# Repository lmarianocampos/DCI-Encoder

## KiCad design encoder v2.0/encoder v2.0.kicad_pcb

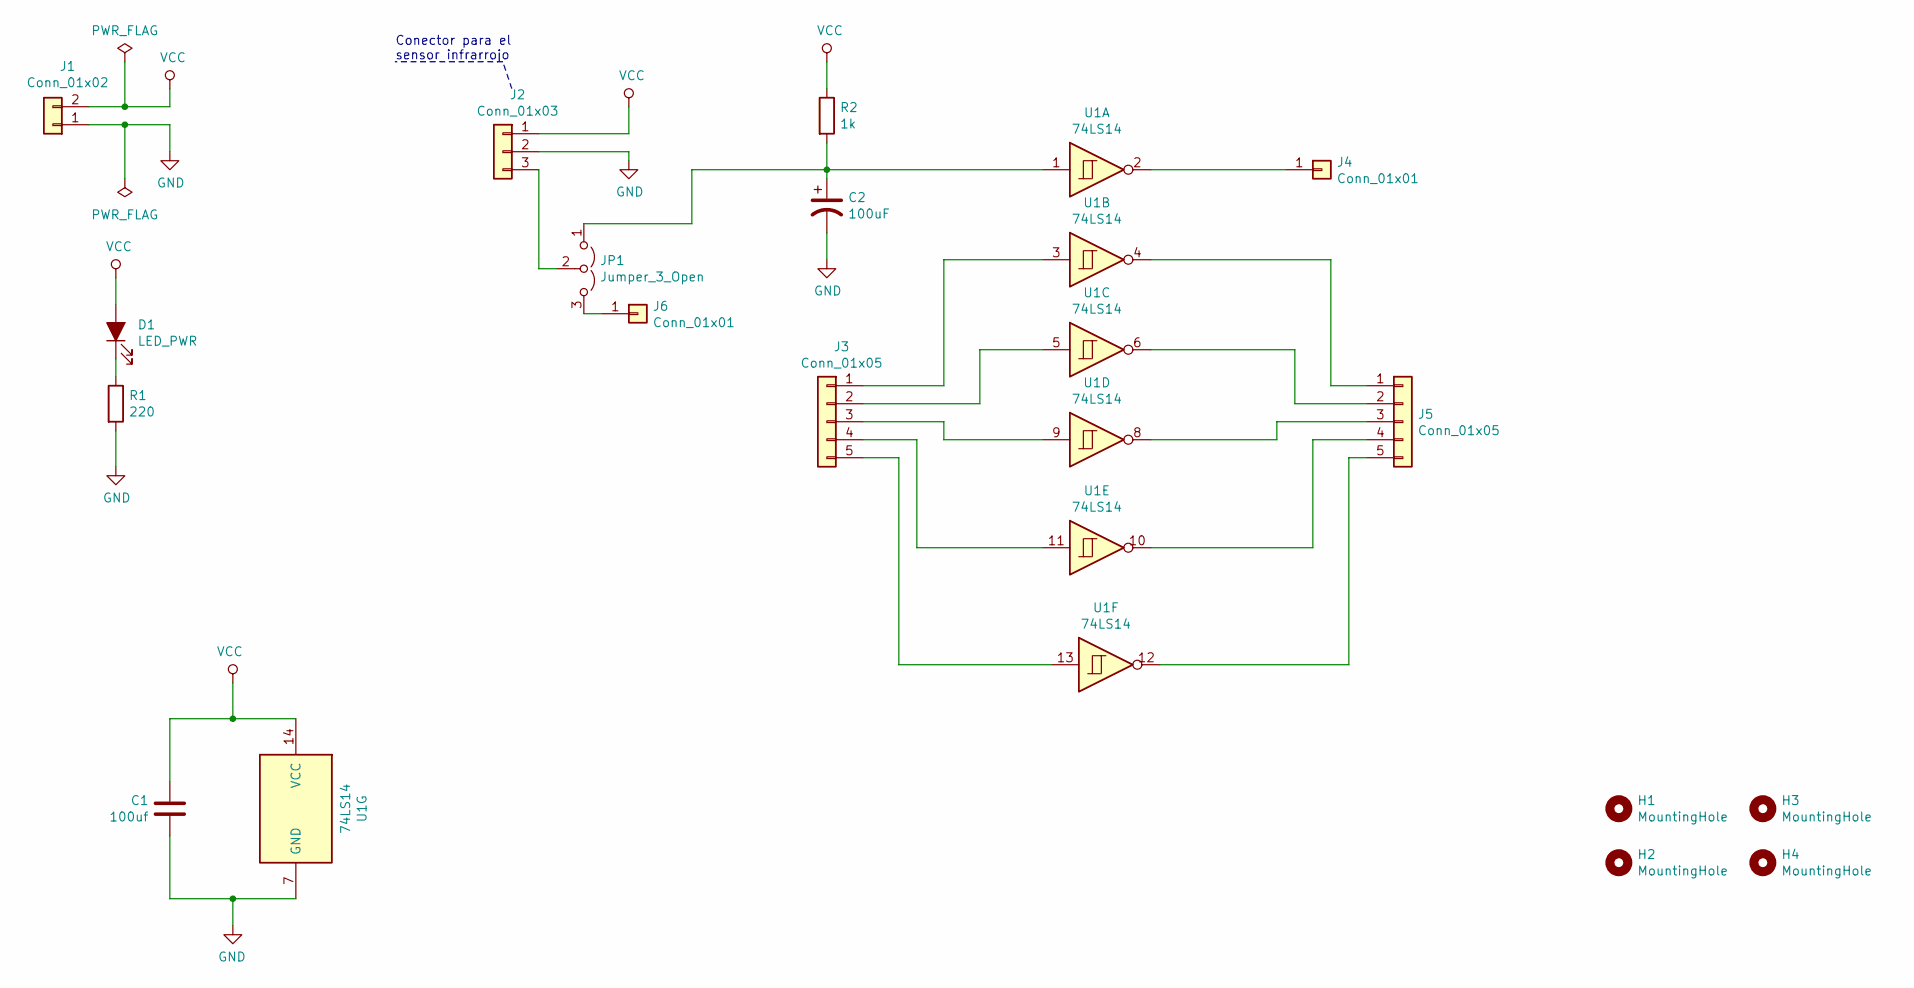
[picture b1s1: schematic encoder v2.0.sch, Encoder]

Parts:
C1: 100uf; C_Disc_D5.0mm_W2.5mm_P2.50mm
C2: 100uF; C_Radial_D6.3mm_H11.0mm_P2.50mm
D1: LED_PWR; LED_D5.0mm
H1, H2, H3, H4: MountingHole; MountingHole_3mm_Pad
J1: Conn_01x02; dg126
J2: Conn_01x03; PinSocket_1x03_P2.54mm_Vertical
J3, J5: Conn_01x05; PinHeader_1x05_P2.54mm_Vertical
J4, J6: Conn_01x01; PinHeader_1x01_P2.54mm_Vertical
JP1: Jumper_3_Open; PinHeader_1x03_P2.54mm_Vertical
R1: 220; R_Axial_DIN0207_L6.3mm_D2.5mm_P10.16mm_Horizontal
R2: 1k; R_Axial_DIN0207_L6.3mm_D2.5mm_P10.16mm_Horizontal
U1: 74LS14; DIP-14_W7.62mm_Socket

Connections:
GND: C1.2, C2.2, J1.1, J2.2, R1.2, U1.7 (GND)
unnamed: C2.1, JP1.1 (A), R2.2, U1.1
unnamed: D1.1 (K), R1.1
unnamed: J2.3, JP1.2 (C)
unnamed: J3.1, U1.3
unnamed: J3.2, U1.5
unnamed: J3.3, U1.9
unnamed: J3.4, U1.11
unnamed: J3.5, U1.13
unnamed: J4.1, U1.2
unnamed: J5.1, U1.4
unnamed: J5.2, U1.6
unnamed: J5.3, U1.8
unnamed: J5.4, U1.10
unnamed: J5.5, U1.12
unnamed: J6.1, JP1.3 (B)
VCC: C1.1, D1.2 (A), J1.2, J2.1, R2.1, U1.14 (VCC)

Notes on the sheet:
Conector para el sensor infrarrojo

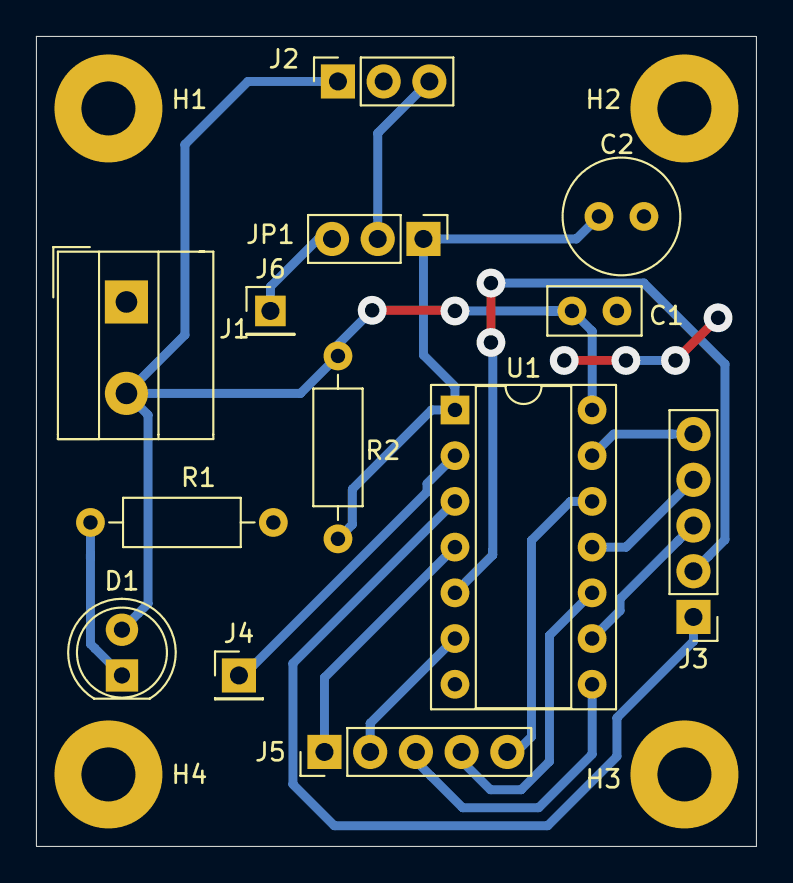
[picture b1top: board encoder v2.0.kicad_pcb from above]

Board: 2 copper layers, 40.0 x 45.0 mm, 17 parts (0 on the bottom side), 17 nets.

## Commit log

2020-05-31 mi segundo commit de inicio
2020-05-31 finalizando el ruteo
2020-06-01 Ruteo finalizado - realizar última verificación
2020-06-03 Ruteo finalizado y realizar una verificación
